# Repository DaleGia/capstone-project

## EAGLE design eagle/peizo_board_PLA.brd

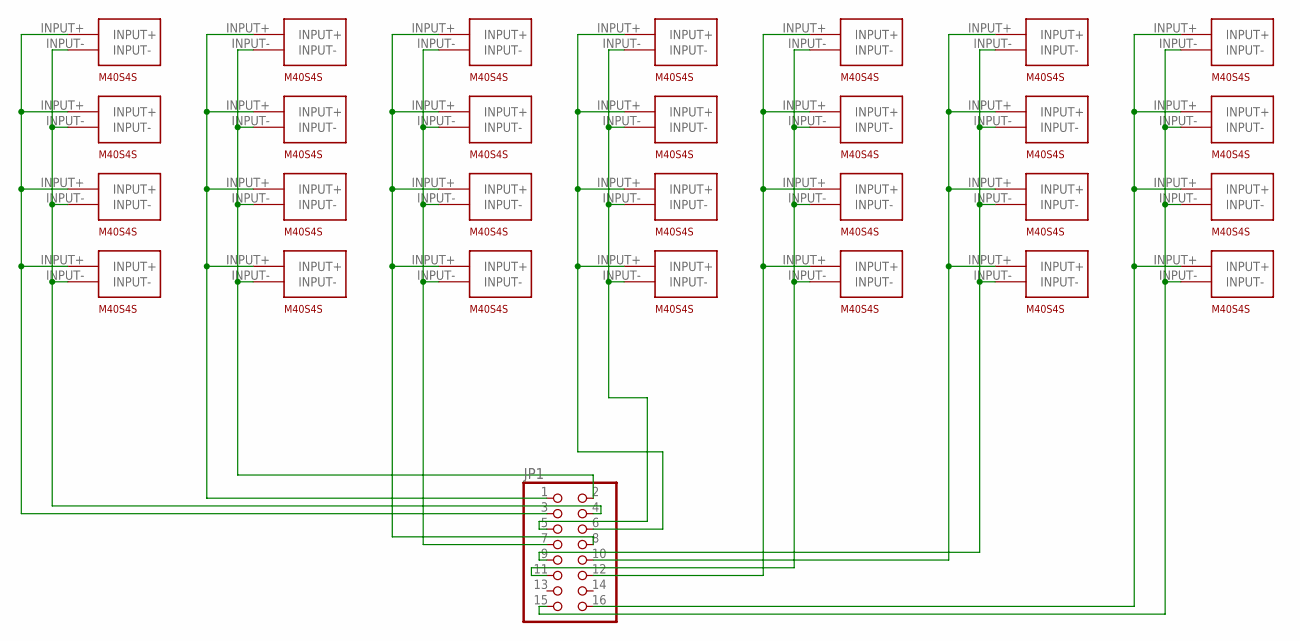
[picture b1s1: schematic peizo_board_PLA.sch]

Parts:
JP1: PINHD-2X8; 2X08
U$1, U$2, U$3, U$4, U$5, U$6, U$7, U$8, U$9, U$10, U$11, U$12, U$13, U$14, U$15, U$16, U$17, U$18, U$19, U$20, U$21, U$22, U$23, U$24, U$25, U$26, U$27, U$28: MA40S4S

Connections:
unnamed: JP1.4, U$1.INPUT-, U$2.INPUT-, U$3.INPUT-, U$4.INPUT-
unnamed: JP1.3, U$1.INPUT+, U$2.INPUT+, U$3.INPUT+, U$4.INPUT+
unnamed: JP1.2, U$5.INPUT-, U$6.INPUT-, U$7.INPUT-, U$8.INPUT-
unnamed: JP1.1, U$5.INPUT+, U$6.INPUT+, U$7.INPUT+, U$8.INPUT+
unnamed: JP1.7, U$9.INPUT-, U$10.INPUT-, U$11.INPUT-, U$12.INPUT-
unnamed: JP1.8, U$9.INPUT+, U$10.INPUT+, U$11.INPUT+, U$12.INPUT+
unnamed: JP1.5, U$13.INPUT-, U$14.INPUT-, U$15.INPUT-, U$16.INPUT-
unnamed: JP1.6, U$13.INPUT+, U$14.INPUT+, U$15.INPUT+, U$16.INPUT+
unnamed: JP1.11, U$17.INPUT-, U$18.INPUT-, U$19.INPUT-, U$20.INPUT-
unnamed: JP1.12, U$17.INPUT+, U$18.INPUT+, U$19.INPUT+, U$20.INPUT+
unnamed: JP1.9, U$21.INPUT-, U$22.INPUT-, U$23.INPUT-, U$24.INPUT-
unnamed: JP1.10, U$21.INPUT+, U$22.INPUT+, U$23.INPUT+, U$24.INPUT+
unnamed: JP1.15, U$25.INPUT-, U$26.INPUT-, U$27.INPUT-, U$28.INPUT-
unnamed: JP1.16, U$25.INPUT+, U$26.INPUT+, U$27.INPUT+, U$28.INPUT+

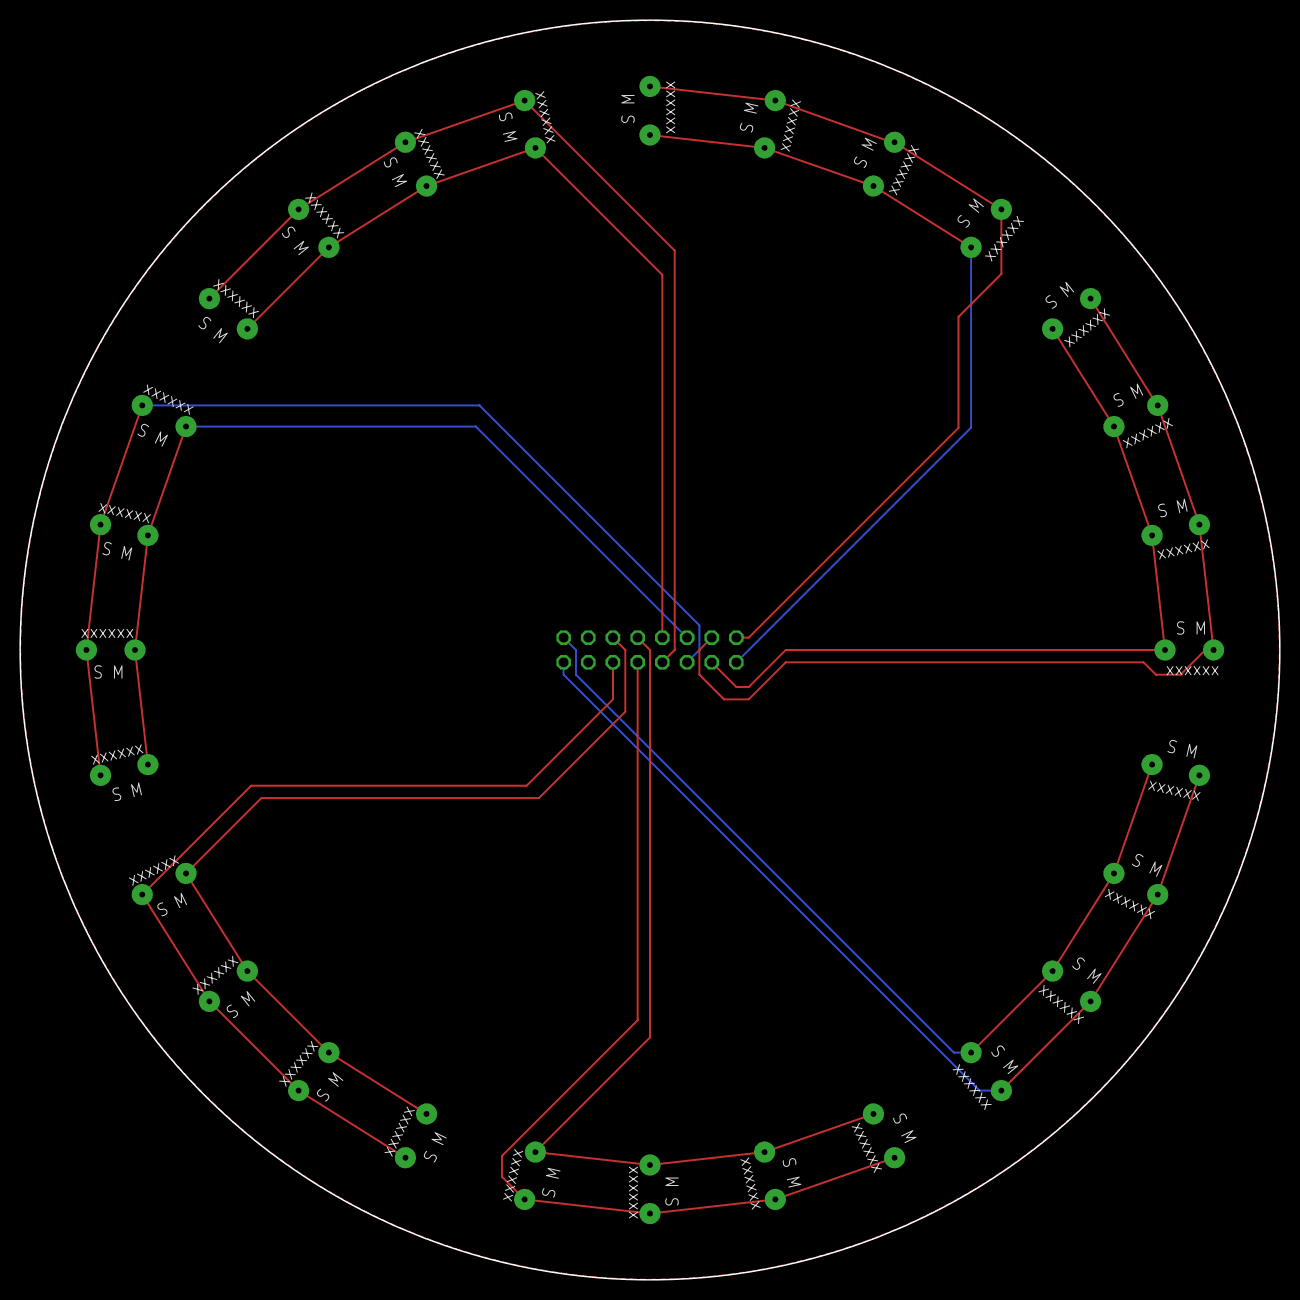
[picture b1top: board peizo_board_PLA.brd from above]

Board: 2 copper layers, 129.6 x 129.6 mm, 29 parts (1 on the bottom side), 14 nets.

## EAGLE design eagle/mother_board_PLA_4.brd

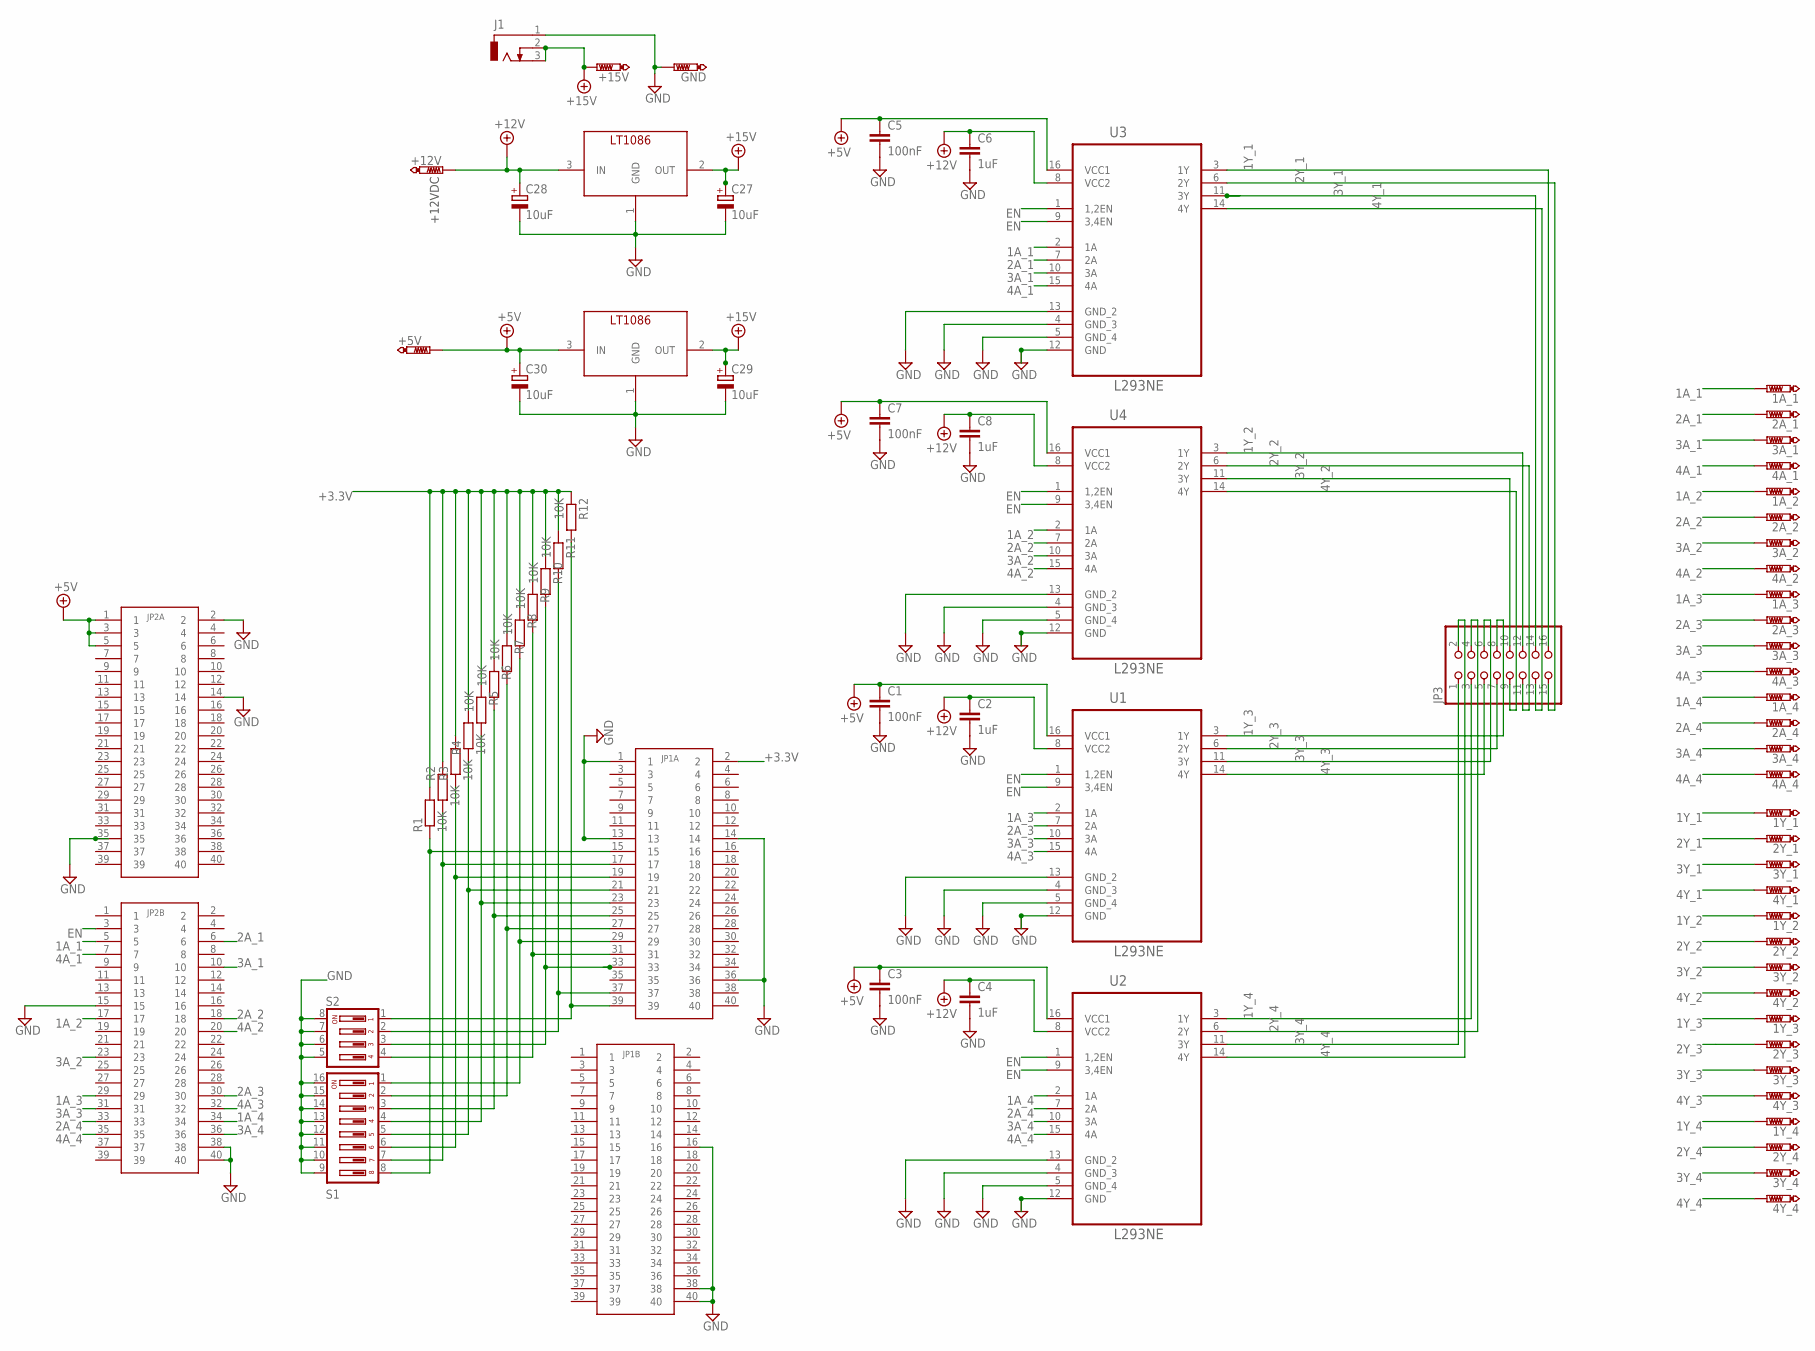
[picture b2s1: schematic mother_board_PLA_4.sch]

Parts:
1A_1, 1A_2, 1A_3, 1A_4, 1Y_1, 1Y_2, 1Y_3, 1Y_4, 2A_1, 2A_2, 2A_3, 2A_4, 2Y_1, 2Y_2, 2Y_3, 2Y_4, 3A_1, 3A_2, 3A_3, 3A_4, 3Y_1, 3Y_2, 3Y_3, 3Y_4, 4A_1, 4A_2, 4A_3, 4A_4, 4Y_1, 4Y_2, 4Y_3, 4Y_4: PTR1PAD1-20Y; P1-20Y
+5V, +12V, +15V: PTR1PAD1-20Y; P1-20Y
C1, C3, C5, C7: 100nF; C050-030X075
C2, C4, C6, C8: 1uF; C050-030X075
C27, C28, C29, C30: 10uF; E5-10,5
GND: PTR1PAD1-20Y; P1-20Y
J1: DCJ0303
JP1A, JP1B, JP2A, JP2B: PIN_HEADER_2MM
JP3: PINHD-2X8; 2X08
R1, R2, R3, R4, R5, R6, R7, R8, R9, R10, R11, R12: 10K; 0207/10
S1: DIP04YL
S2: DIP08YL
U1, U2, U3, U4: L293NE; DIP254P762X508-16
U$4, U$6: LT1086LT1086-V; TO220_VERTICAL

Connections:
1A_1: 1A_1.TP, JP2B.5, U3.2 (1A)
1A_2: 1A_2.TP, JP2B.17, U4.2 (1A)
1A_3: 1A_3.TP, JP2B.29, U1.2 (1A)
1A_4: 1A_4.TP, JP2B.34, U2.2 (1A)
1Y_1: 1Y_1.TP, JP3.16, U3.3 (1Y)
1Y_2: 1Y_2.TP, JP3.12, U4.3 (1Y)
1Y_3: 1Y_3.TP, JP3.8, U1.3 (1Y)
1Y_4: 1Y_4.TP, JP3.3, U2.3 (1Y)
2A_1: 2A_1.TP, JP2B.6, U3.7 (2A)
2A_2: 2A_2.TP, JP2B.18, U4.7 (2A)
2A_3: 2A_3.TP, JP2B.30, U1.7 (2A)
2A_4: 2A_4.TP, JP2B.33, U2.7 (2A)
2Y_1: 2Y_1.TP, JP3.15, U3.6 (2Y)
2Y_2: 2Y_2.TP, JP3.11, U4.6 (2Y)
2Y_3: 2Y_3.TP, JP3.7, U1.6 (2Y)
2Y_4: 2Y_4.TP, JP3.4, U2.6 (2Y)
3A_1: 3A_1.TP, JP2B.10, U3.10 (3A)
3A_2: 3A_2.TP, JP2B.23, U4.10 (3A)
3A_3: 3A_3.TP, JP2B.31, U1.10 (3A)
3A_4: 3A_4.TP, JP2B.36, U2.10 (3A)
3Y_1: 3Y_1.TP, JP3.14, U3.11 (3Y)
3Y_2: 3Y_2.TP, JP3.10, U4.11 (3Y)
3Y_3: 3Y_3.TP, JP3.6, U1.11 (3Y)
3Y_4: 3Y_4.TP, JP3.1, U2.11 (3Y)
4A_1: 4A_1.TP, JP2B.7, U3.15 (4A)
4A_2: 4A_2.TP, JP2B.20, U4.15 (4A)
4A_3: 4A_3.TP, JP2B.32, U1.15 (4A)
4A_4: 4A_4.TP, JP2B.35, U2.15 (4A)
4Y_1: 4Y_1.TP, JP3.13, U3.14 (4Y)
4Y_2: 4Y_2.TP, JP3.9, U4.14 (4Y)
4Y_3: 4Y_3.TP, JP3.5, U1.14 (4Y)
4Y_4: 4Y_4.TP, JP3.2, U2.14 (4Y)
+3.3V: JP1A.2, R1.2, R2.2, R3.2, R4.2, R5.1, R6.1, R7.1, R8.1, R9.1, R10.1, R11.1, R12.1
+5V: +5V.TP, C1.1, C3.1, C5.1, C7.1, C30.+, JP2A.1, JP2A.3, JP2A.5, U1.16 (VCC1), U2.16 (VCC1), U3.16 (VCC1), U4.16 (VCC1), U$4.3 (IN)
+12V: +12V.TP, C2.1, C4.1, C6.1, C8.1, C28.+, U1.8 (VCC2), U2.8 (VCC2), U3.8 (VCC2), U4.8 (VCC2), U$6.3 (IN)
+15V: +15V.TP, C27.+, C29.+, J1.2, J1.3, U$4.2 (OUT), U$6.2 (OUT)
EN: JP2B.3, U1.1 (1,2EN), U1.9 (3,4EN), U2.1 (1,2EN), U2.9 (3,4EN), U3.1 (1,2EN), U3.9 (3,4EN), U4.1 (1,2EN), U4.9 (3,4EN)
GND: C1.2, C2.2, C3.2, C4.2, C5.2, C6.2, C7.2, C8.2, C27.-, C28.-, C29.-, C30.-, GND.TP, J1.1, JP1A.1, JP1A.13, JP1A.14, JP1A.36, JP1B.16, JP1B.38, JP1B.40, JP2A.2, JP2A.14, JP2A.35, JP2B.15, JP2B.38, JP2B.40, S1.5, S1.6, S1.7, S1.8, S2.9, S2.10, S2.11, S2.12, S2.13, S2.14, S2.15, S2.16, U1.4 (GND_3), U1.5 (GND_4), U1.12 (GND), U1.13 (GND_2), U2.4 (GND_3), U2.5 (GND_4), U2.12 (GND), U2.13 (GND_2), U3.4 (GND_3), U3.5 (GND_4), U3.12 (GND), U3.13 (GND_2), U4.4 (GND_3), U4.5 (GND_4), U4.12 (GND), U4.13 (GND_2), U$4.1 (GND), U$6.1 (GND)
unnamed: JP1A.37, R11.2, S1.2
unnamed: JP1A.39, R12.2, S1.1
unnamed: JP1A.33, R10.2, S1.3
unnamed: JP1A.31, R9.2, S1.4
unnamed: JP1A.15, R1.1, S2.8
unnamed: JP1A.17, R2.1, S2.7
unnamed: JP1A.19, R3.1, S2.6
unnamed: JP1A.21, R4.1, S2.5
unnamed: JP1A.23, R5.2, S2.4
unnamed: JP1A.25, R6.2, S2.3
unnamed: JP1A.27, R7.2, S2.2
unnamed: JP1A.29, R8.2, S2.1

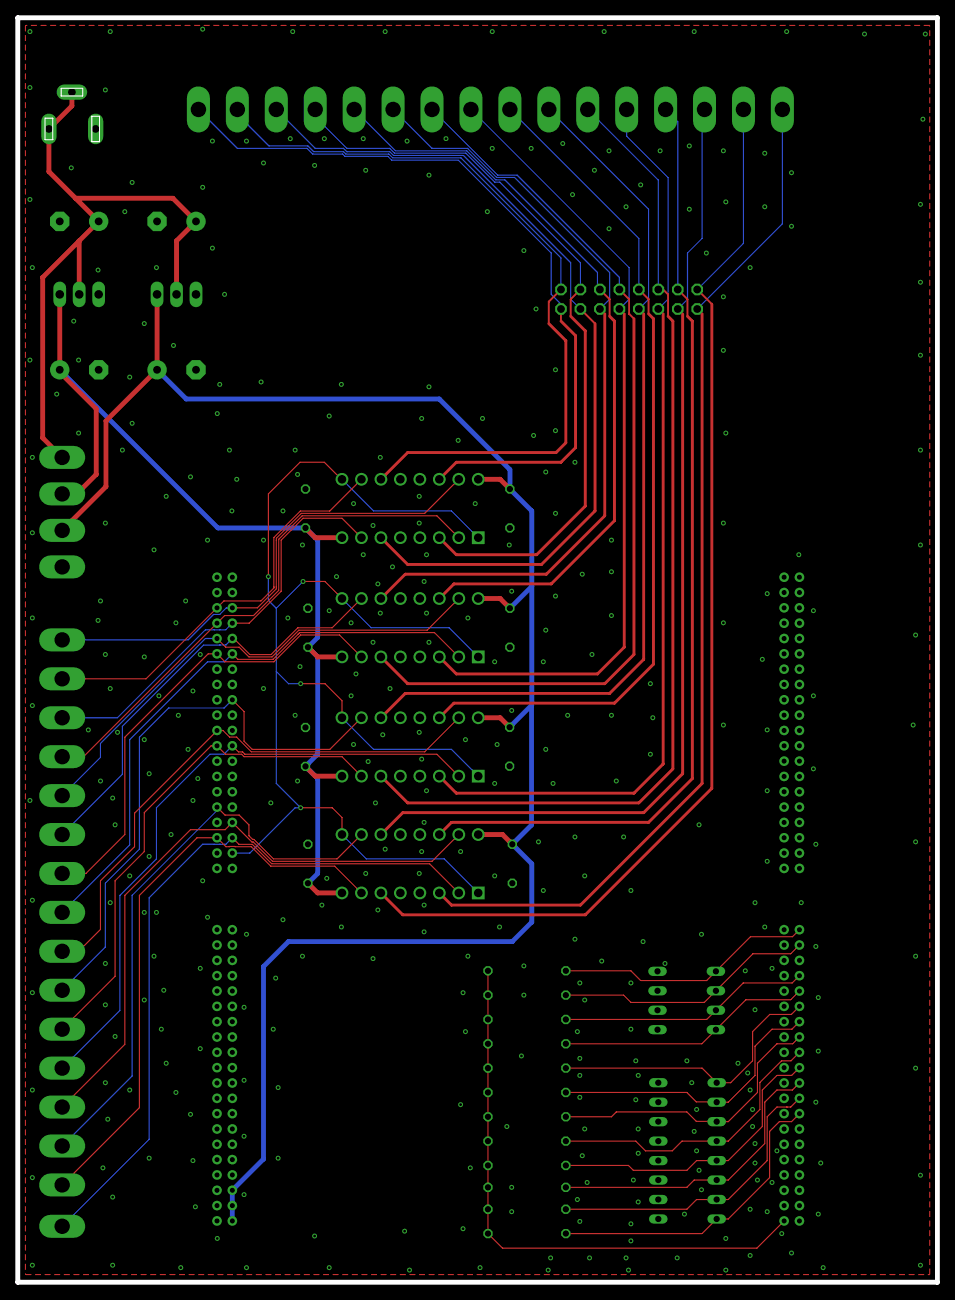
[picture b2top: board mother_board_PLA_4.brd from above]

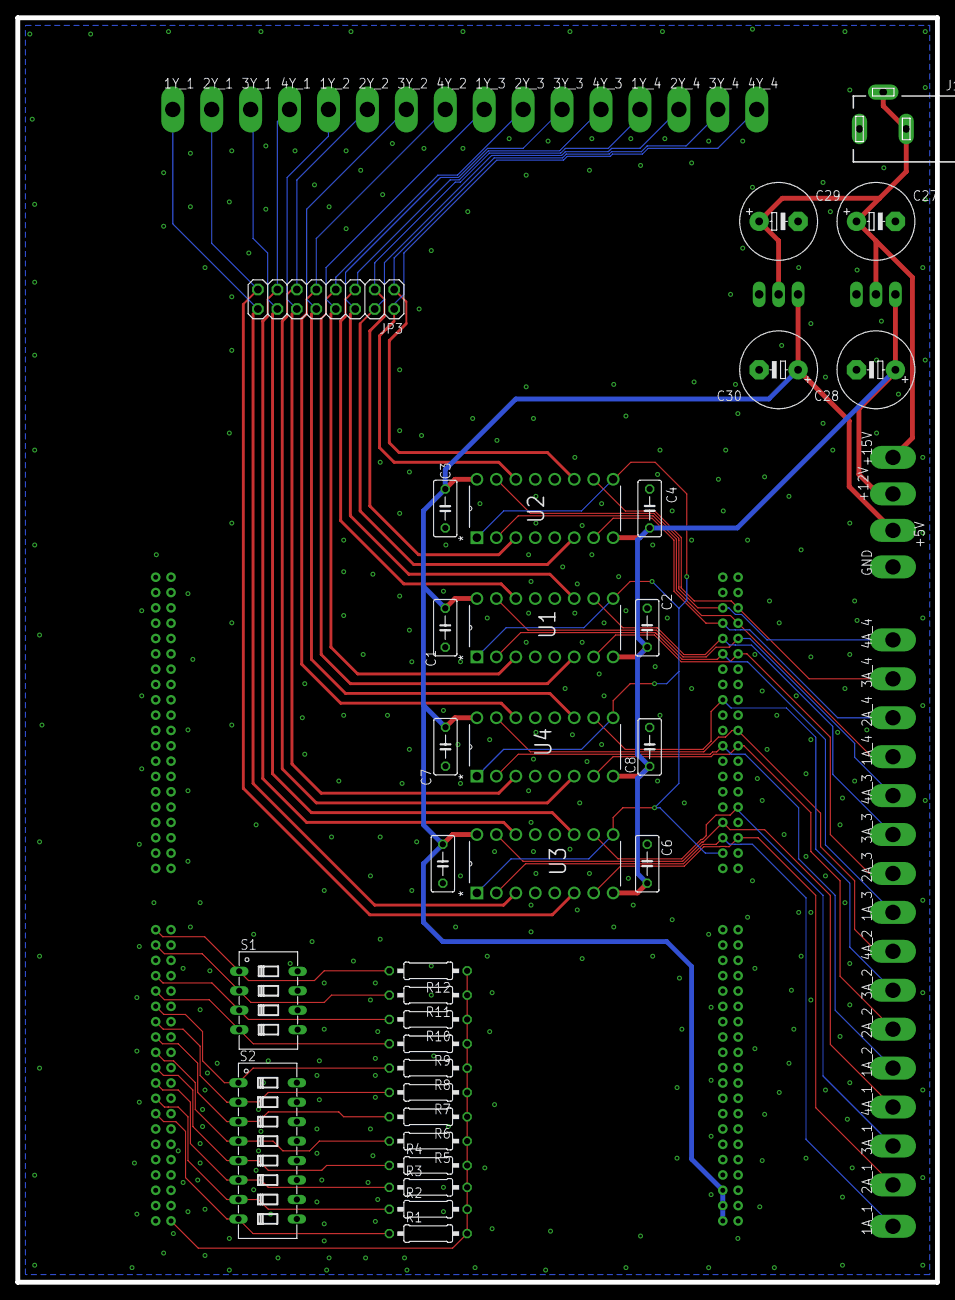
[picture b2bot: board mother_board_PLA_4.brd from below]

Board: 2 copper layers, 120.0 x 165.0 mm, 74 parts (70 on the bottom side), 50 nets.

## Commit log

2018-11-06 Adding project files
